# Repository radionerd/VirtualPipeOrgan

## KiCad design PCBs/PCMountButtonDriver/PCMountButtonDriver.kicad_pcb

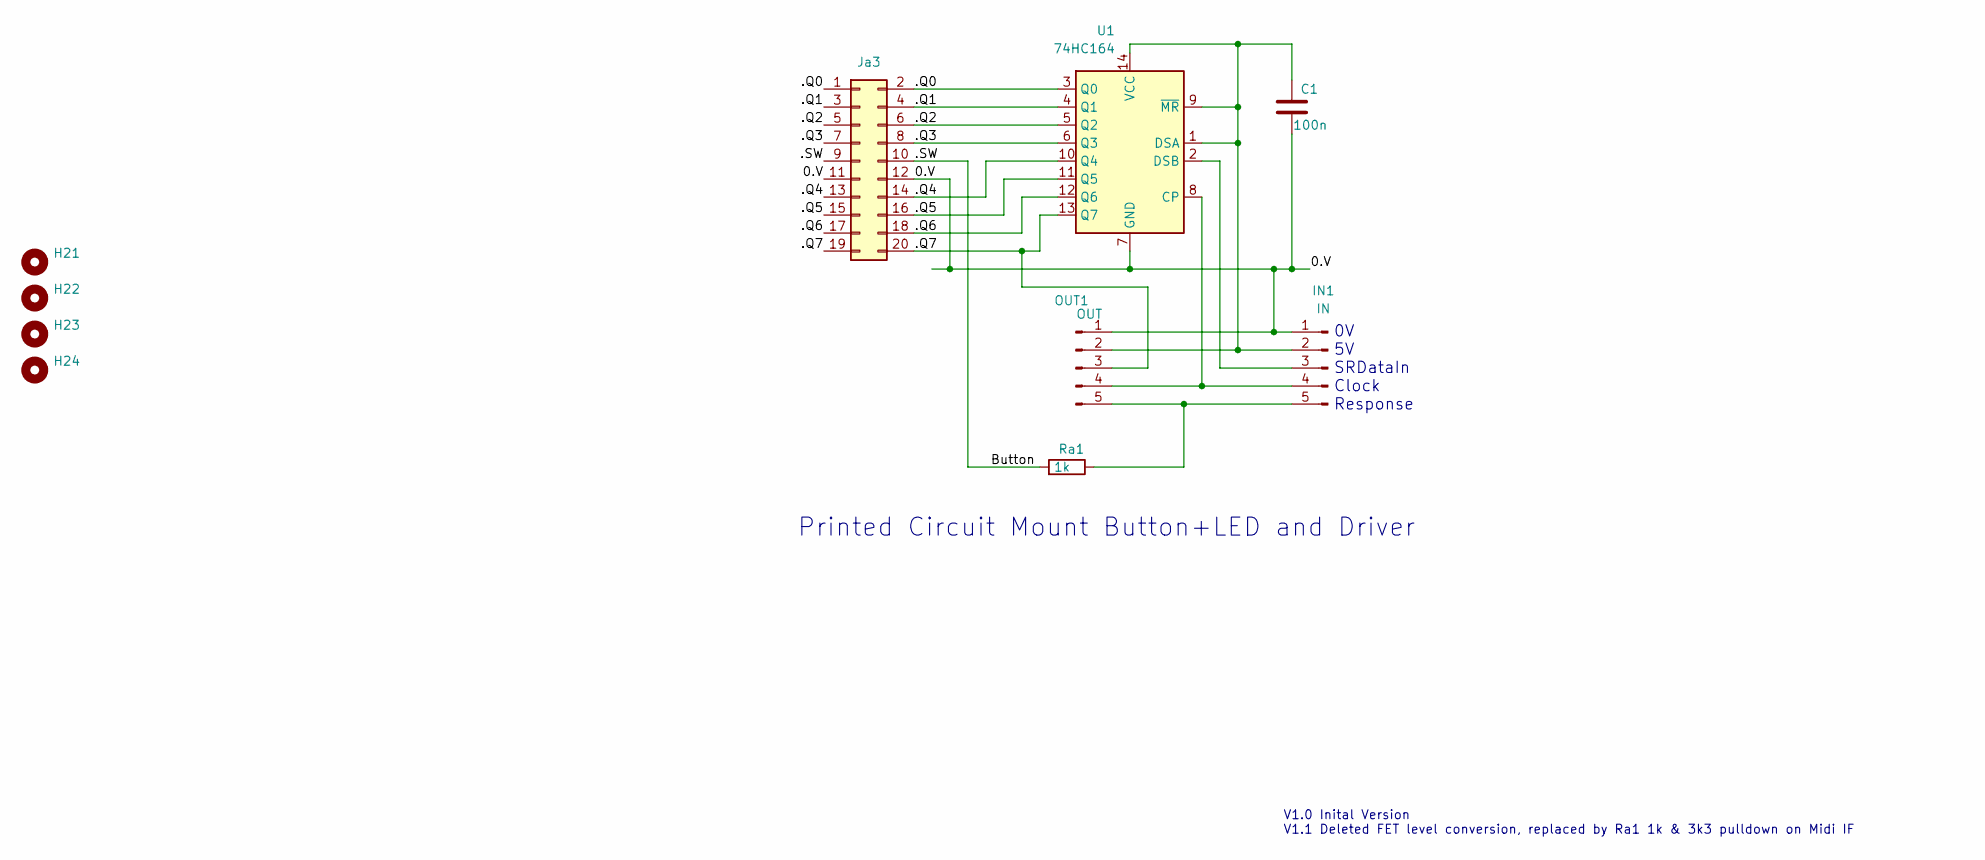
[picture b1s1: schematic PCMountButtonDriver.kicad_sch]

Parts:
C1: 100n; C_0805_2012Metric_Pad1.18x1.45mm_HandSolder
H21, H22, H23, H24: MountingHole; MountingHole_3.2mm_M3
IN1: IN; PinHeader_1x05_P2.54mm_Vertical
Ja3: Conn_02x10_Odd_Even; PinHeader_2x10_P2.54mm_Vertical
OUT1: OUT; PinHeader_1x05_P2.54mm_Vertical
Ra1: 1k; R_0805_2012Metric_Pad1.20x1.40mm_HandSolder
U1: 74HC164; DIP-14_W7.62mm_LongPads

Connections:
/0.V: C1.2, IN1.1, Ja3.11, Ja3.12, OUT1.1, U1.7 (GND)
/.Q0: Ja3.1, Ja3.2, U1.3 (Q0)
/.Q1: Ja3.3, Ja3.4, U1.4 (Q1)
/.Q2: Ja3.5, Ja3.6, U1.5 (Q2)
/.Q3: Ja3.7, Ja3.8, U1.6 (Q3)
/.Q4: Ja3.13, Ja3.14, U1.10 (Q4)
/.Q5: Ja3.15, Ja3.16, U1.11 (Q5)
/.Q6: Ja3.17, Ja3.18, U1.12 (Q6)
/.Q7: Ja3.19, Ja3.20, OUT1.3, U1.13 (Q7)
/.SW: Ja3.9, Ja3.10, Ra1.2
unnamed: C1.1, IN1.2, OUT1.2, U1.1 (DSA), U1.9 (~MR), U1.14 (VCC)
unnamed: IN1.3, U1.2 (DSB)
unnamed: IN1.4, OUT1.4, U1.8 (CP)
unnamed: IN1.5, OUT1.5, Ra1.1

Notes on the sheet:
V1.0 Inital Version V1.1 Deleted FET level conversion, replaced by Ra1 1k & 3k3 pulldown on Midi IF
Printed Circuit Mount Button+LED and Driver
0V 5V SRDataIn Clock Response

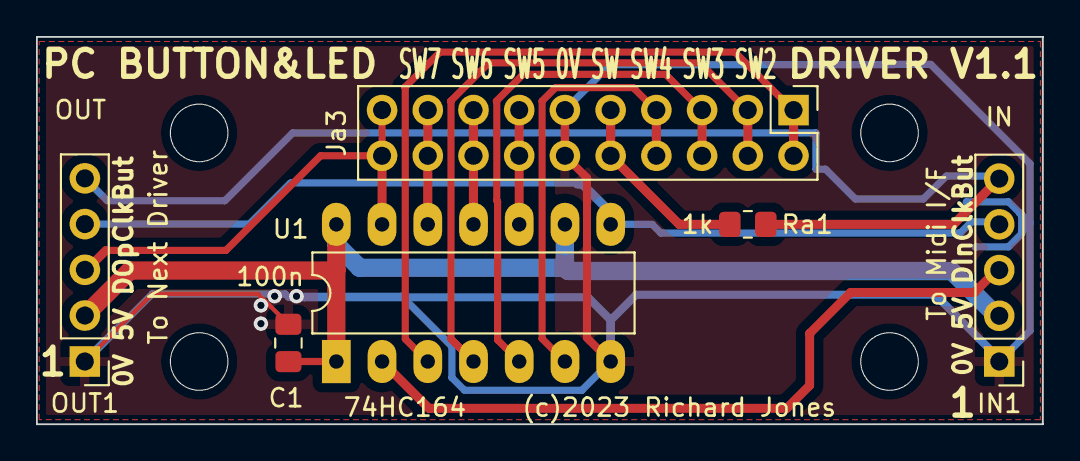
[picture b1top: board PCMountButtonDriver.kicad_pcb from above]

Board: 2 copper layers, 55.9 x 21.5 mm, 10 parts (0 on the bottom side), 14 nets.

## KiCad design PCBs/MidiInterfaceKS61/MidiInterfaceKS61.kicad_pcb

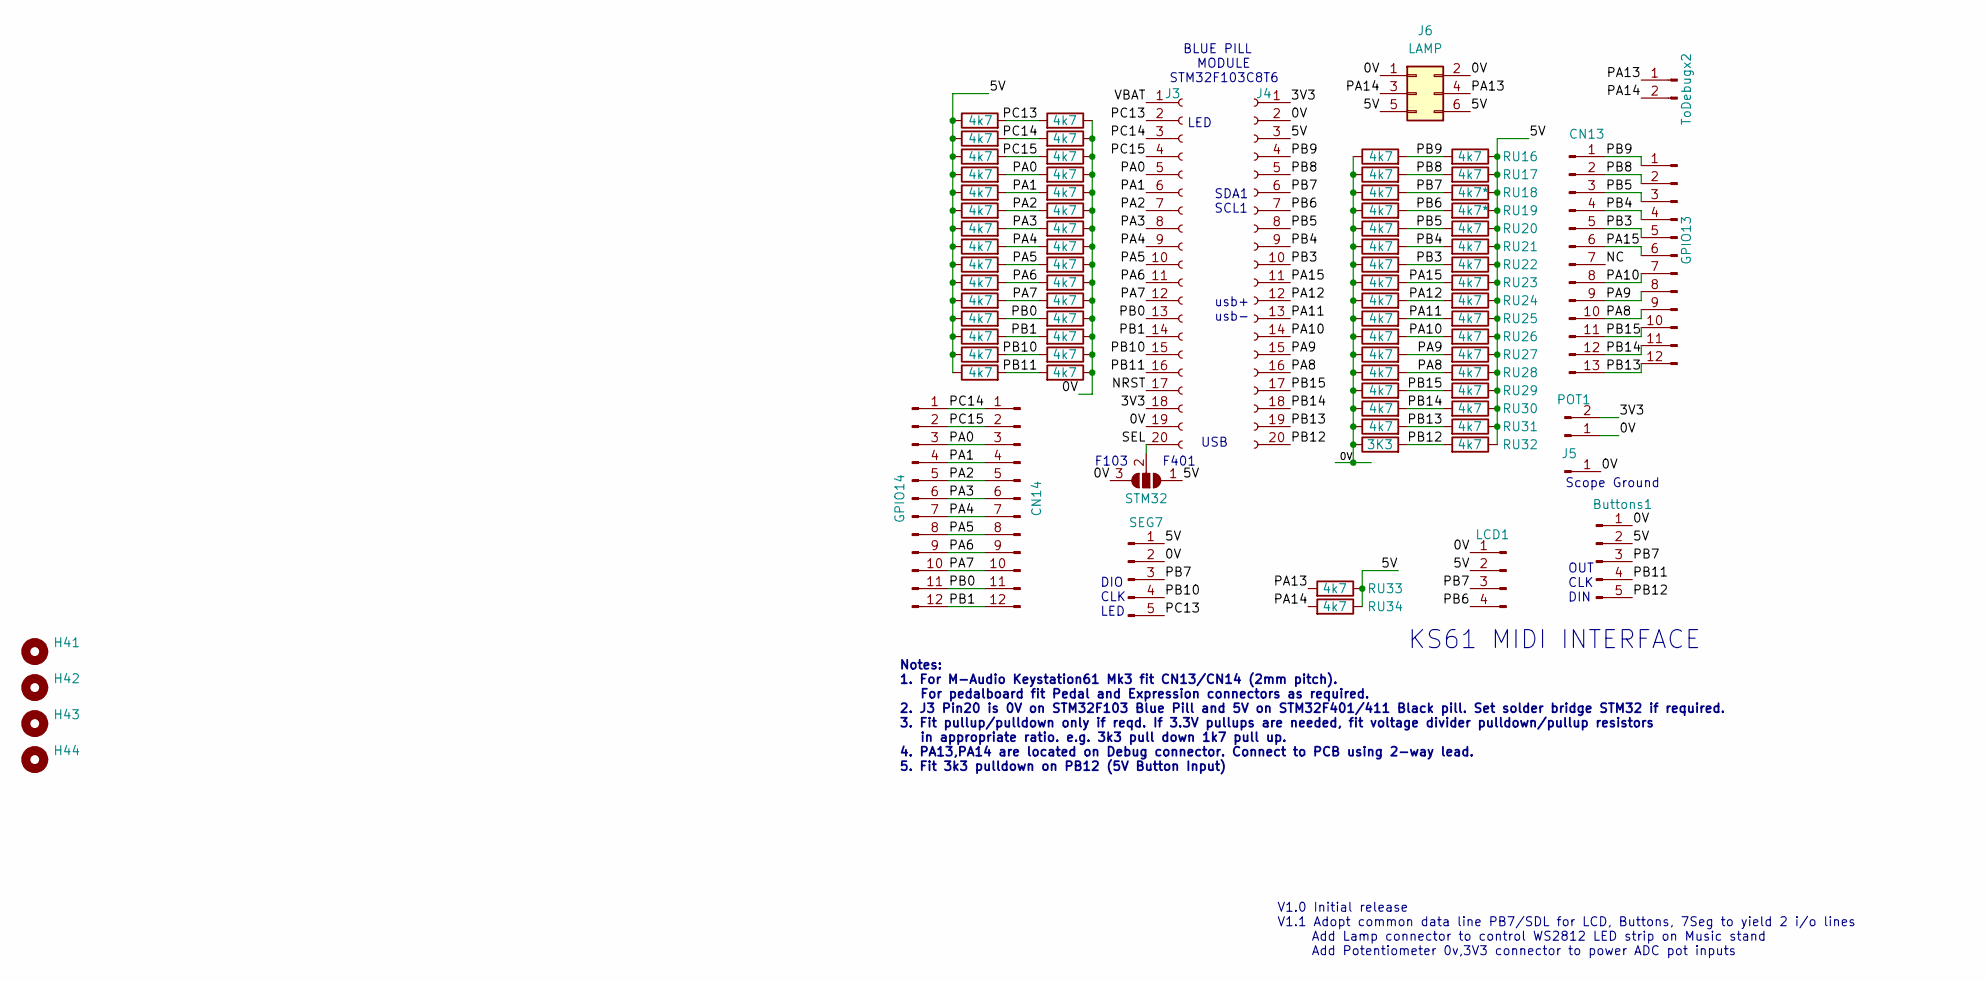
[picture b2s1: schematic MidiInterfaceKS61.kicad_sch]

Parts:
Buttons1: Conn_01x05_Male; PinHeader_1x05_P2.54mm_Vertical
CN13: Conn_01x13_Male; PinHeader_1x13_P2.00mm_Vertical
CN14: Conn_01x12_Male; PinHeader_1x12_P2.00mm_Vertical
GPIO13, GPIO14: Conn_01x12_Male; PinHeader_1x12_P2.54mm_Vertical
H41, H42, H43, H44: MountingHole; MountingHole_3.2mm_M3
J3, J4: Conn_01x20_Female; PinHeader_1x20_P2.54mm_Vertical
J5: Conn_01x01_Male; PinHeader_1x01_P2.54mm_Vertical
J6: LAMP; PinHeader_2x03_P2.54mm_Vertical
LCD1: Conn_01x04_Male; PinHeader_1x04_P2.54mm_Vertical
POT1: Conn_01x02_Male; PinHeader_1x02_P2.54mm_Vertical
RD1, RD2, RD3, RD4, RD5, RD6, RD7, RD8, RD9, RD10, RD11, RD12, RD13, RD14, RD15, RD16, RD17, RD18, RD19, RD20, RD21, RD22, RD23, RD24, RD25, RD26, RD27, RD28, RD29, RD30, RD31: 4k7; R_0805_2012Metric_Pad1.20x1.40mm_HandSolder
RD32: 3K3; R_0805_2012Metric_Pad1.20x1.40mm_HandSolder
RU1, RU2, RU3, RU4, RU5, RU6, RU7, RU8, RU9, RU10, RU11, RU12, RU13, RU14, RU15, RU16, RU17, RU20, RU21, RU22, RU23, RU24, RU25, RU26, RU27, RU28, RU29, RU30, RU31, RU32, RU33, RU34: 4k7; R_0805_2012Metric_Pad1.20x1.40mm_HandSolder
RU18, RU19: 4k7*; R_0805_2012Metric_Pad1.20x1.40mm_HandSolder
SEG7: Conn_01x05_Male; PinHeader_1x05_P2.54mm_Vertical
STM32: SolderJumper_3_Open; SolderJumper-3_P1.3mm_Open_RoundedPad1.0x1.5mm_NumberLabels
ToDebugx2: Conn_01x02_Male; PinHeader_1x02_P2.54mm_Vertical

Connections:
/0V: Buttons1.1, J3.19, J4.2, J5.1, J6.1, J6.2, LCD1.1, POT1.1, RD1.1, RD2.1, RD3.1, RD4.1, RD5.1, RD6.1, RD7.1, RD8.1, RD9.1, RD10.1, RD11.1, RD12.1, RD13.1, RD14.1, RD15.1, RD16.1, RD17.1, RD18.1, RD19.1, RD20.1, RD21.1, RD22.1, RD23.1, RD24.1, RD25.1, RD26.1, RD27.1, RD28.1, RD29.1, RD30.1, RD31.1, RD32.1, SEG7.2, STM32.3 (B)
/3V3: J3.18, J4.1, POT1.2
/5V: Buttons1.2, J4.3, J6.5, J6.6, LCD1.2, RU1.1, RU2.1, RU3.1, RU4.1, RU5.1, RU6.1, RU7.1, RU8.1, RU9.1, RU10.1, RU11.1, RU12.1, RU13.1, RU14.1, RU15.1, RU16.1, RU17.1, RU18.1, RU19.1, RU20.1, RU21.1, RU22.1, RU23.1, RU24.1, RU25.1, RU26.1, RU27.1, RU28.1, RU29.1, RU30.1, RU31.1, RU32.1, RU33.1, RU34.1, SEG7.1, STM32.1 (A)
/NC: CN13.7
/NRST: J3.17
/PA0: CN14.3, GPIO14.3, J3.5, RD4.2, RU4.2
/PA1: CN14.4, GPIO14.4, J3.6, RD5.2, RU5.2
/PA2: CN14.5, GPIO14.5, J3.7, RD6.2, RU6.2
/PA3: CN14.6, GPIO14.6, J3.8, RD7.2, RU7.2
/PA4: CN14.7, GPIO14.7, J3.9, RD8.2, RU8.2
/PA5: CN14.8, GPIO14.8, J3.10, RD9.2, RU9.2
/PA6: CN14.9, GPIO14.9, J3.11, RD10.2, RU10.2
/PA7: CN14.10, GPIO14.10, J3.12, RD11.2, RU11.2
/PA8: CN13.10, GPIO13.9, J4.16, RD28.2, RU28.2
/PA9: CN13.9, GPIO13.8, J4.15, RD27.2, RU27.2
/PA10: CN13.8, GPIO13.7, J4.14, RD26.2, RU26.2
/PA11: J4.13, RD25.2, RU25.2
/PA12: J4.12, RD24.2, RU24.2
/PA13: J6.4, RU33.2, ToDebugx2.1
/PA14: J6.3, RU34.2, ToDebugx2.2
/PA15: CN13.6, GPIO13.6, J4.11, RD23.2, RU23.2
/PB0: CN14.11, GPIO14.11, J3.13, RD12.2, RU12.2
/PB1: CN14.12, GPIO14.12, J3.14, RD13.2, RU13.2
/PB3: CN13.5, GPIO13.5, J4.10, RD22.2, RU22.2
/PB4: CN13.4, GPIO13.4, J4.9, RD21.2, RU21.2
/PB5: CN13.3, GPIO13.3, J4.8, RD20.2, RU20.2
/PB6: J4.7, LCD1.4, RD19.2, RU19.2
/PB7: Buttons1.3, J4.6, LCD1.3, RD18.2, RU18.2, SEG7.3
/PB8: CN13.2, GPIO13.2, J4.5, RD17.2, RU17.2
/PB9: CN13.1, GPIO13.1, J4.4, RD16.2, RU16.2
/PB10: J3.15, RD14.2, RU14.2, SEG7.4
/PB11: Buttons1.4, J3.16, RD15.2, RU15.2
/PB12: Buttons1.5, J4.20, RD32.2, RU32.2
/PB13: CN13.13, GPIO13.12, J4.19, RD31.2, RU31.2
/PB14: CN13.12, GPIO13.11, J4.18, RD30.2, RU30.2
/PB15: CN13.11, GPIO13.10, J4.17, RD29.2, RU29.2
/PC13: J3.2, RD1.2, RU1.2, SEG7.5
/PC14: CN14.1, GPIO14.1, J3.3, RD2.2, RU2.2
/PC15: CN14.2, GPIO14.2, J3.4, RD3.2, RU3.2
/SEL: J3.20, STM32.2 (C)
/VBAT: J3.1

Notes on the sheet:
BLUE PILL MODULE STM32F103C8T6
OUT CLK DIN
KS61 MIDI INTERFACE
usb+ usb-
DIO CLK LED
LED
Notes: 1. For M-Audio Keystation61 Mk3 fit CN13/CN14 (2mm pitch). For pedalboard fit Pedal and Expression connectors as required. 2. J3 Pin20 is 0V on STM32F103 Blue Pill and 5V on STM32F401/411 Black pill. Set solder bridge STM32 if required. 3. Fit pullup/pulldown only if reqd. If 3.3V pullups ar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
Scope Ground
SDA1 SCL1
V1.0 Initial release V1.1 Adopt common data line PB7/SDL for LCD, Buttons, 7Seg to yield 2 i/o lines Add Lamp connector to control WS2812 LED strip on Music stand Add Potentiometer 0v,3V3 connector to power ADC pot inputs
USB
F103 F401

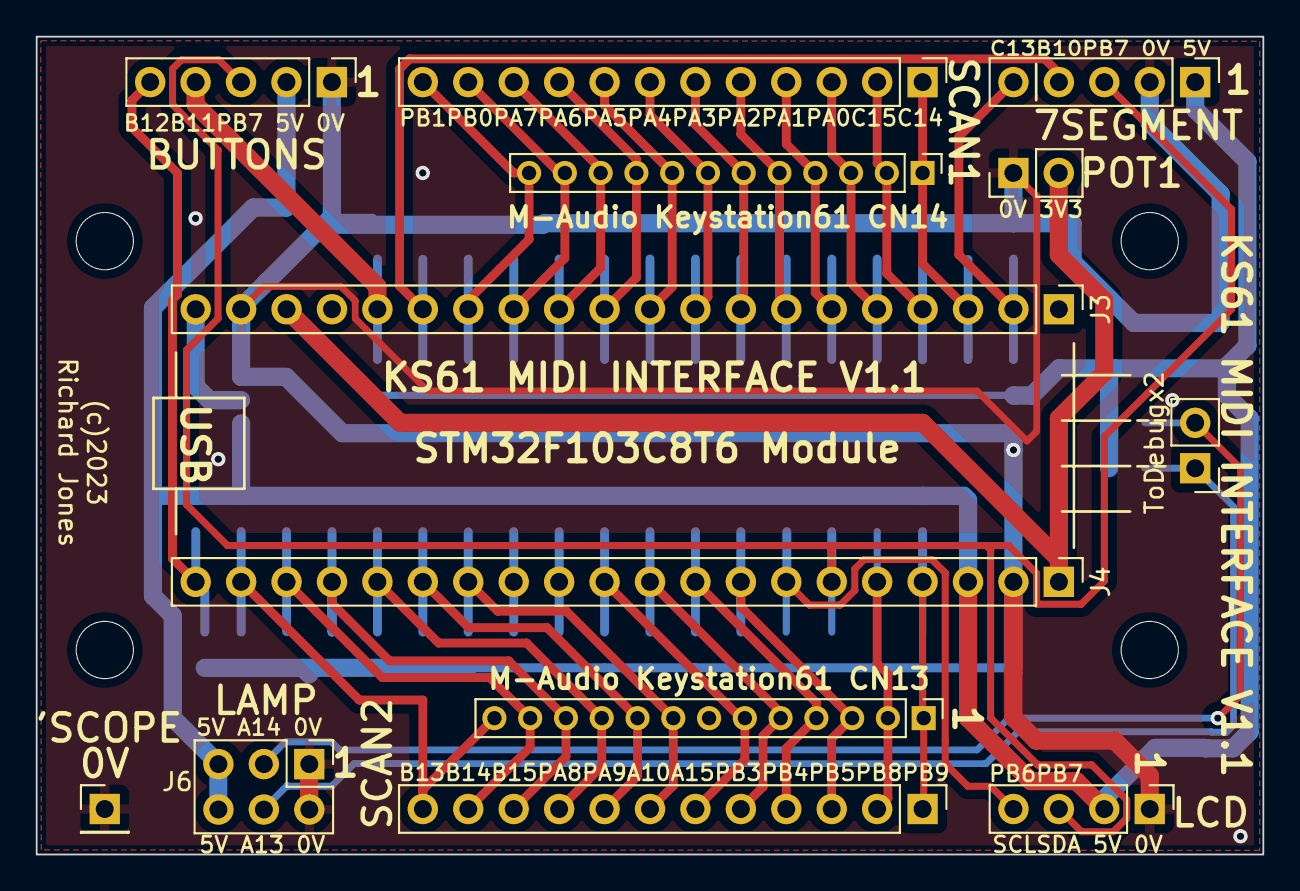
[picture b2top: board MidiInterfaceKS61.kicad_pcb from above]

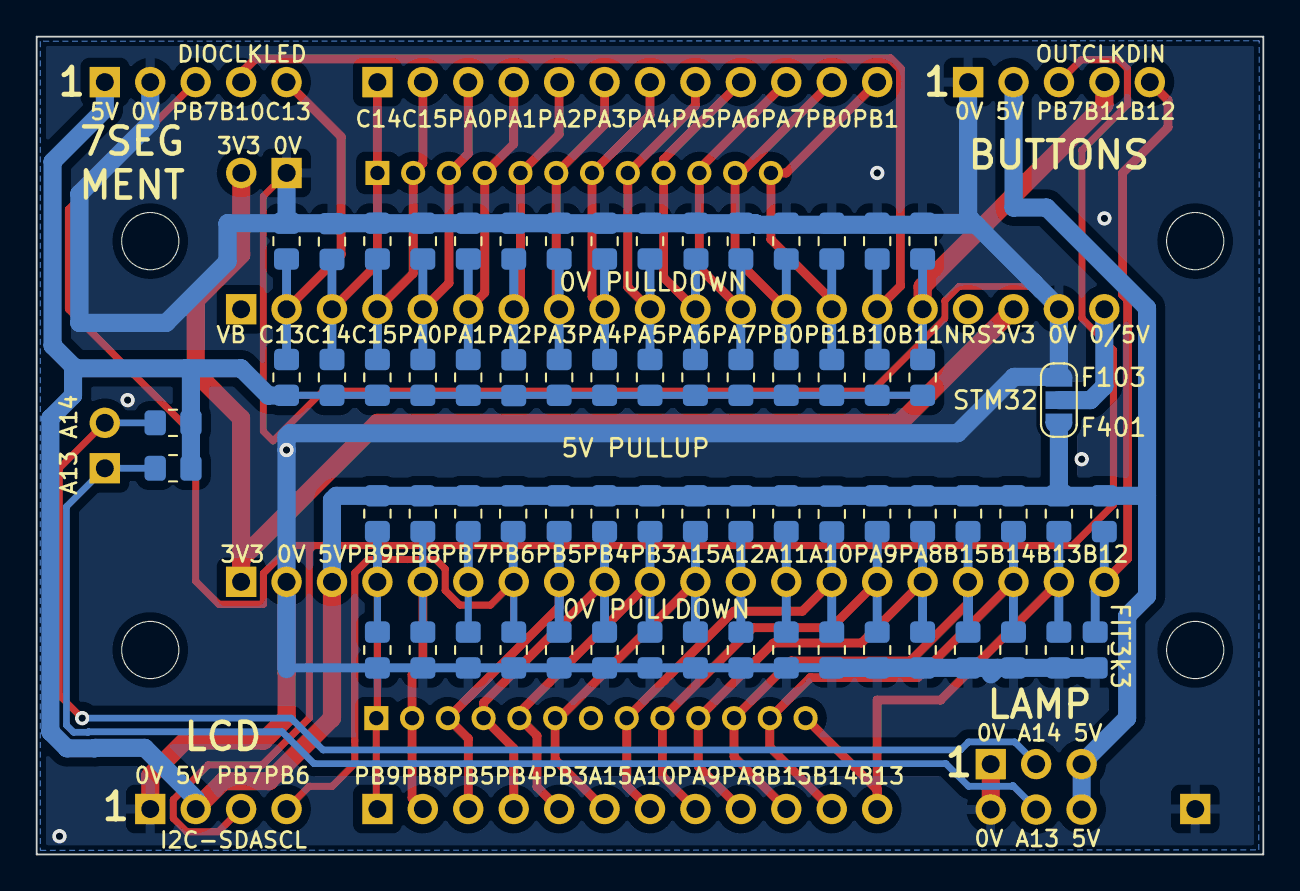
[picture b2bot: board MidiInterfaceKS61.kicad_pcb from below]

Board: 2 copper layers, 68.6 x 45.7 mm, 84 parts (67 on the bottom side), 38 nets.

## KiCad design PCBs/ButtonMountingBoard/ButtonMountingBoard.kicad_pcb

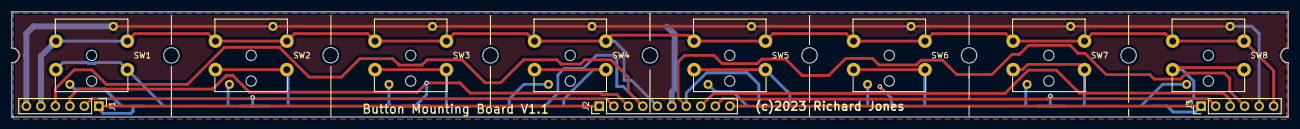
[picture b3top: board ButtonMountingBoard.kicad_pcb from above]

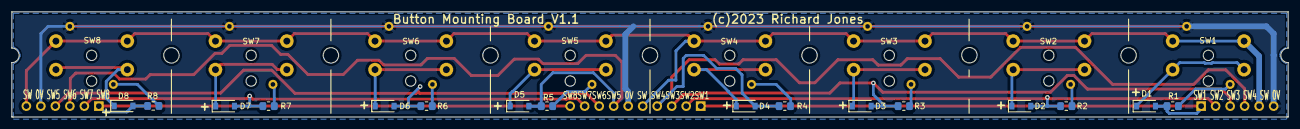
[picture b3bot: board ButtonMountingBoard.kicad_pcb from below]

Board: 2 copper layers, 223.5 x 18.4 mm, 34 parts (16 on the bottom side), 26 nets.

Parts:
D1, D2, D3, D4, D5, D6, D7, D8: 1N4148; D_SOD-123
H1, H2, H3, H4, H5, H6, H7: MountingHole; MountingHole_2.7mm_M2.5
J1, J3: Conn_01x06_Male; PinHeader_1x06_P2.54mm_Vertical
J2: Conn_01x10_Male; PinHeader_1x10_P2.54mm_Vertical
R1, R2, R3, R4, R5, R6, R7, R8: 560; R_0805_2012Metric_Pad1.20x1.40mm_HandSolder
SW1, SW2, SW3, SW4, SW5, SW6, SW7, SW8: SW_TACT_LED; TS12_TS27

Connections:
/LED: J1.6, J2.6, J3.5, SW1.5, SW2.5, SW3.5, SW4.5, SW5.5, SW6.5, SW7.5, SW8.5
/SW: J1.5, J2.5, J3.6, SW1.3, SW1.4, SW2.3, SW2.4, SW3.3, SW3.4, SW4.3, SW4.4, SW5.3, SW5.4, SW6.3, SW6.4, SW7.3, SW7.4, SW8.3, SW8.4
unnamed: D1.1 (K), SW1.1, SW1.2
unnamed: D1.2 (A), J1.1, J2.1, R1.2
unnamed: D2.1 (K), SW2.1, SW2.2
unnamed: D2.2 (A), J1.2, J2.2, R2.2
unnamed: D3.1 (K), SW3.1, SW3.2
unnamed: D3.2 (A), J1.3, J2.3, R3.2
unnamed: D4.1 (K), SW4.1, SW4.2
unnamed: D4.2 (A), J1.4, J2.4, R4.2
unnamed: D5.1 (K), SW5.1, SW5.2
unnamed: D5.2 (A), J2.7, J3.4, R5.2
unnamed: D6.1 (K), SW6.1, SW6.2
unnamed: D6.2 (A), J2.8, J3.3, R6.2
unnamed: D7.1 (K), SW7.1, SW7.2
unnamed: D7.2 (A), J2.9, J3.2, R7.2
unnamed: D8.1 (K), SW8.1, SW8.2
unnamed: D8.2 (A), J2.10, J3.1, R8.2
unnamed: R1.1, SW1.6
unnamed: R2.1, SW2.6
unnamed: R3.1, SW3.6
unnamed: R4.1, SW4.6
unnamed: R5.1, SW5.6
unnamed: R6.1, SW6.6
unnamed: R7.1, SW7.6
unnamed: R8.1, SW8.6

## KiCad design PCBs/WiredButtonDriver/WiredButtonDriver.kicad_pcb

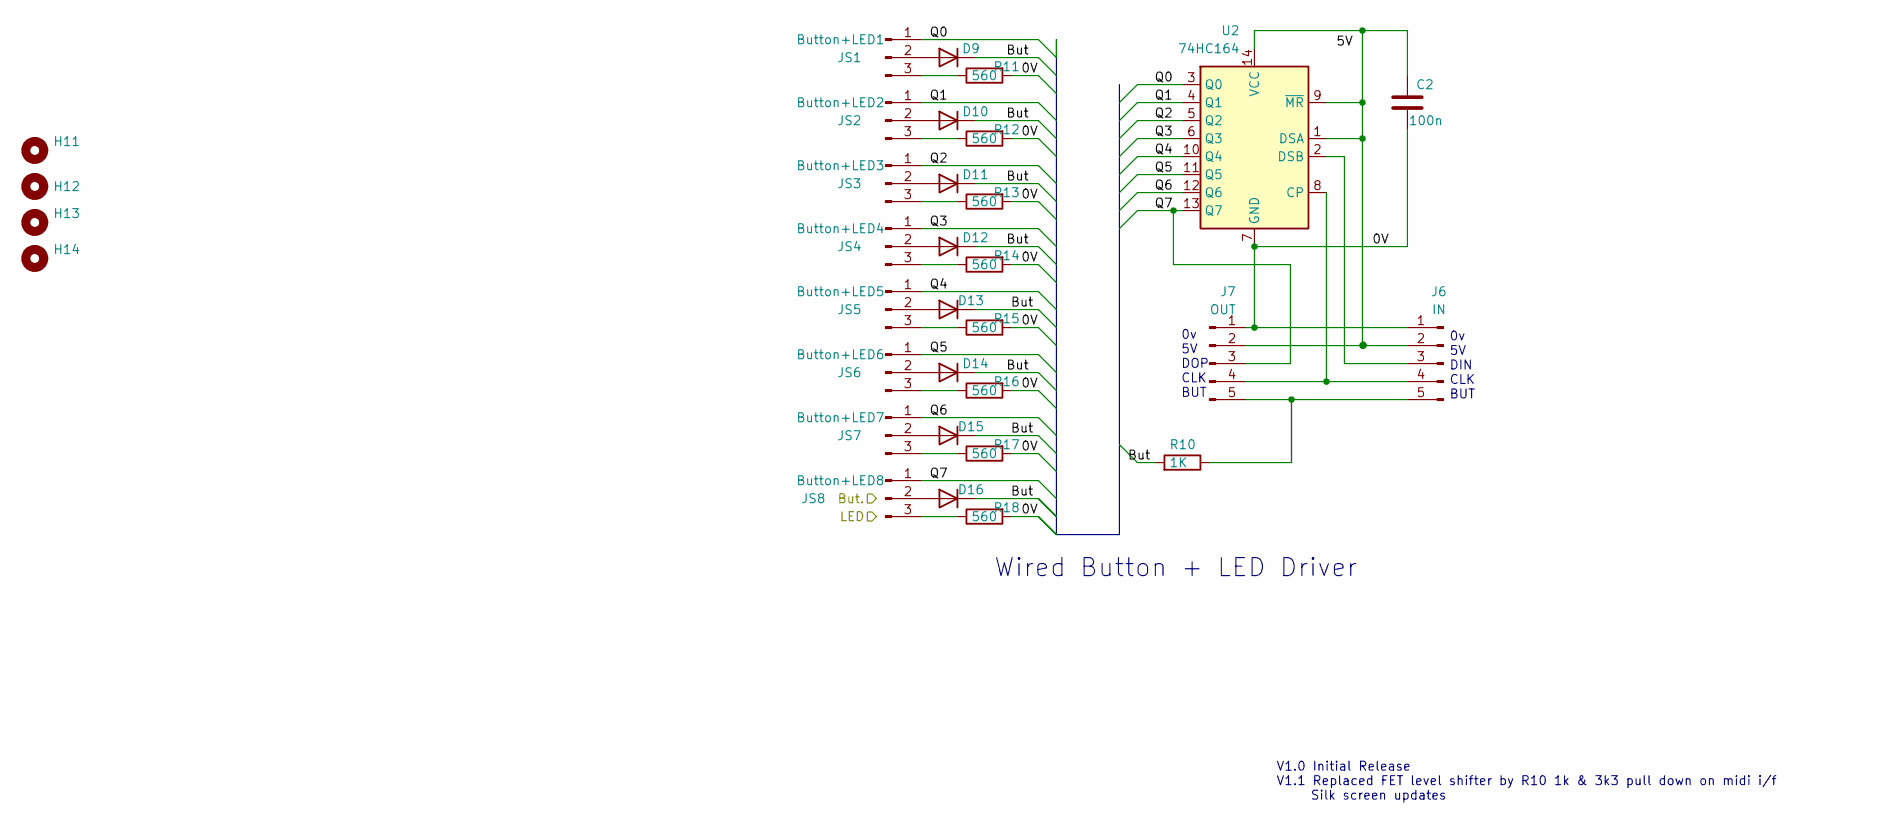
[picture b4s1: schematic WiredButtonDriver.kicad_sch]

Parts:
C2: 100n; C_0805_2012Metric_Pad1.18x1.45mm_HandSolder
D9, D10, D11, D12, D13, D14, D15, D16: 1N4148; D_SOD-123
H11, H12, H13, H14: MountingHole; MountingHole_3.2mm_M3
J6: IN; PinHeader_1x05_P2.54mm_Vertical
J7: OUT; PinHeader_1x05_P2.54mm_Vertical
JS1: Button+LED1; PinHeader_1x03_P2.54mm_Vertical
JS2: Button+LED2; PinHeader_1x03_P2.54mm_Vertical
JS3: Button+LED3; PinHeader_1x03_P2.54mm_Vertical
JS4: Button+LED4; PinHeader_1x03_P2.54mm_Vertical
JS5: Button+LED5; PinHeader_1x03_P2.54mm_Vertical
JS6: Button+LED6; PinHeader_1x03_P2.54mm_Vertical
JS7: Button+LED7; PinHeader_1x03_P2.54mm_Vertical
JS8: Button+LED8; PinHeader_1x03_P2.54mm_Vertical
R10: 1K; R_0805_2012Metric_Pad1.20x1.40mm_HandSolder
R11, R12, R13, R14, R15, R16, R17, R18: 560; R_0805_2012Metric_Pad1.20x1.40mm_HandSolder
U2: 74HC164; DIP-14_W7.62mm_LongPads

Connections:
/0V: C2.2, J6.1, J7.1, R11.2, R12.2, R13.2, R14.2, R15.2, R16.2, R17.2, R18.2, U2.7 (GND)
/But: D9.1 (K), D10.1 (K), D11.1 (K), D12.1 (K), D13.1 (K), D14.1 (K), D15.1 (K), D16.1 (K), R10.2
/Q0: JS1.1, U2.3 (Q0)
/Q1: JS2.1, U2.4 (Q1)
/Q2: JS3.1, U2.5 (Q2)
/Q3: JS4.1, U2.6 (Q3)
/Q4: JS5.1, U2.10 (Q4)
/Q5: JS6.1, U2.11 (Q5)
/Q6: JS7.1, U2.12 (Q6)
/Q7: J7.3, JS8.1, U2.13 (Q7)
unnamed: C2.1, J6.2, J7.2, U2.1 (DSA), U2.9 (~MR), U2.14 (VCC)
unnamed: D9.2 (A), JS1.2
unnamed: D10.2 (A), JS2.2
unnamed: D11.2 (A), JS3.2
unnamed: D12.2 (A), JS4.2
unnamed: D13.2 (A), JS5.2
unnamed: D14.2 (A), JS6.2
unnamed: D15.2 (A), JS7.2
unnamed: D16.2 (A), JS8.2
unnamed: J6.3, U2.2 (DSB)
unnamed: J6.4, J7.4, U2.8 (CP)
unnamed: J6.5, J7.5, R10.1
unnamed: JS1.3, R11.1
unnamed: JS2.3, R12.1
unnamed: JS3.3, R13.1
unnamed: JS4.3, R14.1
unnamed: JS5.3, R15.1
unnamed: JS6.3, R16.1
unnamed: JS7.3, R17.1
unnamed: JS8.3, R18.1

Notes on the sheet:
0v 5V DOP CLK BUT
0v 5V DIN CLK BUT
V1.0 Initial Release V1.1 Replaced FET level shifter by R10 1k & 3k3 pull down on midi i/f Silk screen updates
Wired Button + LED Driver

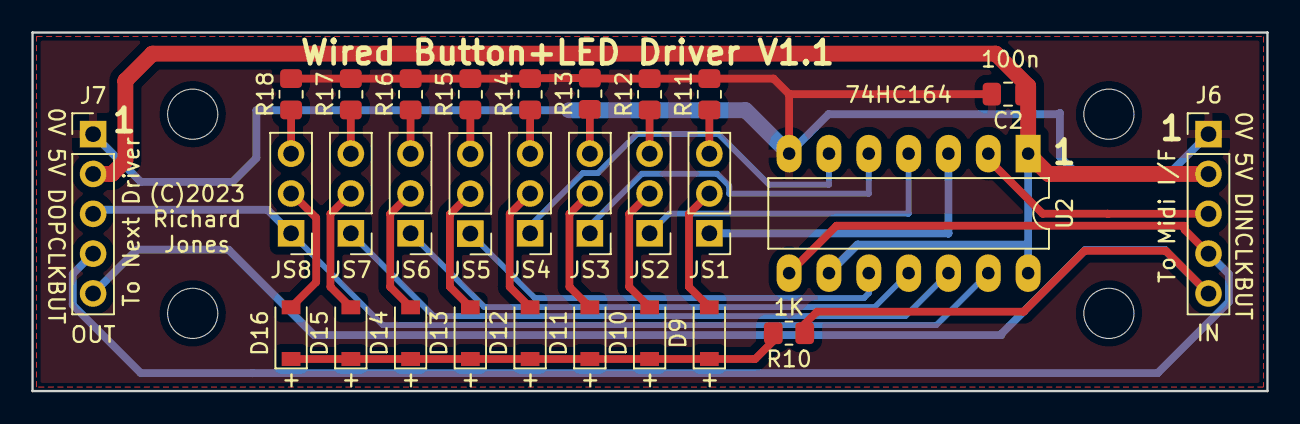
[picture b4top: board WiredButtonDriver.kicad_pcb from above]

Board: 2 copper layers, 78.7 x 22.9 mm, 33 parts (0 on the bottom side), 30 nets.

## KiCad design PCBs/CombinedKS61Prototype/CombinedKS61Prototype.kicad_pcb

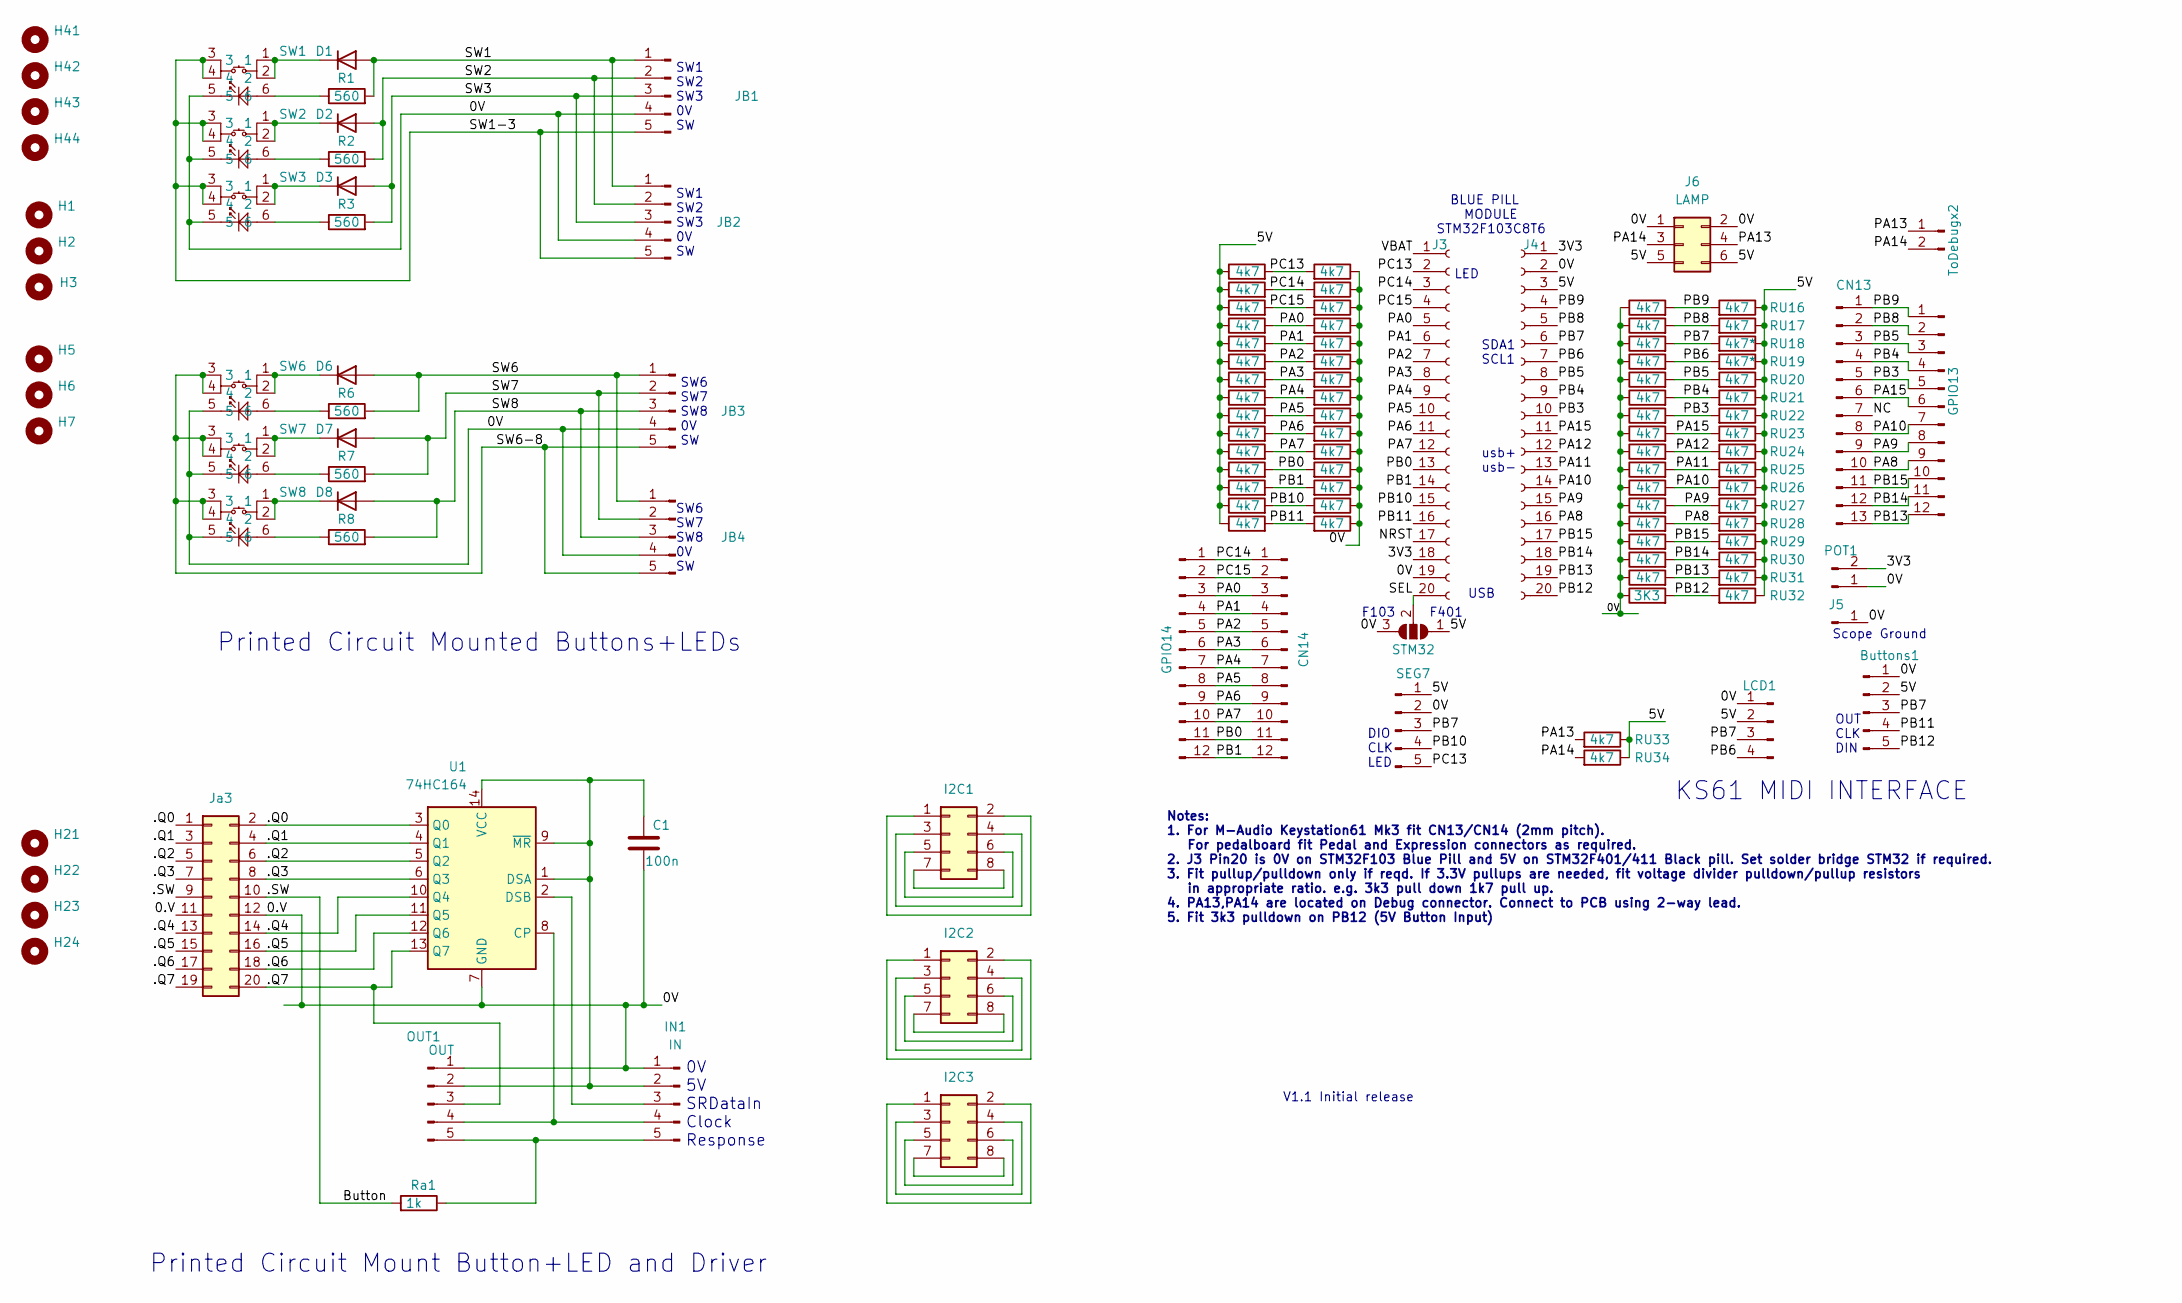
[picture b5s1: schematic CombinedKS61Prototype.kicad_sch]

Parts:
Buttons1: Conn_01x05_Male; PinHeader_1x05_P2.54mm_Vertical
C1: 100n; C_0805_2012Metric_Pad1.18x1.45mm_HandSolder
CN13: Conn_01x13_Male; PinHeader_1x13_P2.00mm_Vertical
CN14: Conn_01x12_Male; PinHeader_1x12_P2.00mm_Vertical
D1, D2, D3, D6, D7, D8: 1N4148; D_SOD-123
GPIO13, GPIO14: Conn_01x12_Male; PinHeader_1x12_P2.54mm_Vertical
H1, H2, H3, H5, H6, H7: MountingHole; MountingHole_2.7mm_M2.5
H21, H22, H23, H24, H41, H42, H43, H44: MountingHole; MountingHole_3.2mm_M3
I2C1, I2C2, I2C3: Conn_02x04_Odd_Even; PinHeader_2x04_P2.54mm_Vertical
IN1: IN; PinHeader_1x05_P2.54mm_Vertical
J3, J4: Conn_01x20_Female; PinHeader_1x20_P2.54mm_Vertical
J5: Conn_01x01_Male; PinHeader_1x01_P2.54mm_Vertical
J6: LAMP; PinHeader_2x03_P2.54mm_Vertical
JB1, JB2, JB3, JB4: Conn_01x05_Male; PinHeader_1x05_P2.54mm_Vertical
Ja3: Conn_02x10_Odd_Even; PinHeader_2x10_P2.54mm_Vertical
LCD1: Conn_01x04_Male; PinHeader_1x04_P2.54mm_Vertical
OUT1: OUT; PinHeader_1x05_P2.54mm_Vertical
POT1: Conn_01x02_Male; PinHeader_1x02_P2.54mm_Vertical
R1, R2, R3, R6, R7, R8: 560; R_0805_2012Metric_Pad1.20x1.40mm_HandSolder
RD1, RD2, RD3, RD4, RD5, RD6, RD7, RD8, RD9, RD10, RD11, RD12, RD13, RD14, RD15, RD16, RD17, RD18, RD19, RD20, RD21, RD22, RD23, RD24, RD25, RD26, RD27, RD28, RD29, RD30, RD31: 4k7; R_0805_2012Metric_Pad1.20x1.40mm_HandSolder
RD32: 3K3; R_0805_2012Metric_Pad1.20x1.40mm_HandSolder
RU1, RU2, RU3, RU4, RU5, RU6, RU7, RU8, RU9, RU10, RU11, RU12, RU13, RU14, RU15, RU16, RU17, RU20, RU21, RU22, RU23, RU24, RU25, RU26, RU27, RU28, RU29, RU30, RU31, RU32, RU33, RU34: 4k7; R_0805_2012Metric_Pad1.20x1.40mm_HandSolder
RU18, RU19: 4k7*; R_0805_2012Metric_Pad1.20x1.40mm_HandSolder
Ra1: 1k; R_0805_2012Metric_Pad1.20x1.40mm_HandSolder
SEG7: Conn_01x05_Male; PinHeader_1x05_P2.54mm_Vertical
STM32: SolderJumper_3_Open; SolderJumper-3_P1.3mm_Open_RoundedPad1.0x1.5mm_NumberLabels
SW1, SW2, SW3, SW6, SW7, SW8: SW_TACT_LED; TS12_TS27
ToDebugx2: Conn_01x02_Male; PinHeader_1x02_P2.54mm_Vertical
U1: 74HC164; DIP-14_W7.62mm_LongPads

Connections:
/0.V: Buttons1.1, C1.2, IN1.1, J3.19, J4.2, J5.1, J6.1, J6.2, JB1.4, JB2.4, JB3.4, JB4.4, Ja3.11, Ja3.12, LCD1.1, OUT1.1, POT1.1, RD1.1, RD2.1, RD3.1, RD4.1, RD5.1, RD6.1, RD7.1, RD8.1, RD9.1, RD10.1, RD11.1, RD12.1, RD13.1, RD14.1, RD15.1, RD16.1, RD17.1, RD18.1, RD19.1, RD20.1, RD21.1, RD22.1, RD23.1, RD24.1, RD25.1, RD26.1, RD27.1, RD28.1, RD29.1, RD30.1, RD31.1, RD32.1, SEG7.2, STM32.3 (B), SW1.5, SW2.5, SW3.5, SW6.5, SW7.5, SW8.5, U1.7 (GND)
/3V3: J3.18, J4.1, POT1.2
/5V: Buttons1.2, J4.3, J6.5, J6.6, LCD1.2, RU1.1, RU2.1, RU3.1, RU4.1, RU5.1, RU6.1, RU7.1, RU8.1, RU9.1, RU10.1, RU11.1, RU12.1, RU13.1, RU14.1, RU15.1, RU16.1, RU17.1, RU18.1, RU19.1, RU20.1, RU21.1, RU22.1, RU23.1, RU24.1, RU25.1, RU26.1, RU27.1, RU28.1, RU29.1, RU30.1, RU31.1, RU32.1, RU33.1, RU34.1, SEG7.1, STM32.1 (A)
/.Q0: Ja3.1, Ja3.2, U1.3 (Q0)
/.Q1: Ja3.3, Ja3.4, U1.4 (Q1)
/.Q2: Ja3.5, Ja3.6, U1.5 (Q2)
/.Q3: Ja3.7, Ja3.8, U1.6 (Q3)
/.Q4: Ja3.13, Ja3.14, U1.10 (Q4)
/.Q5: Ja3.15, Ja3.16, U1.11 (Q5)
/.Q6: Ja3.17, Ja3.18, U1.12 (Q6)
/.Q7: Ja3.19, Ja3.20, OUT1.3, U1.13 (Q7)
/.SW: Ja3.9, Ja3.10, Ra1.2
/NC: CN13.7
/NRST: J3.17
/PA0: CN14.3, GPIO14.3, J3.5, RD4.2, RU4.2
/PA1: CN14.4, GPIO14.4, J3.6, RD5.2, RU5.2
/PA2: CN14.5, GPIO14.5, J3.7, RD6.2, RU6.2
/PA3: CN14.6, GPIO14.6, J3.8, RD7.2, RU7.2
/PA4: CN14.7, GPIO14.7, J3.9, RD8.2, RU8.2
/PA5: CN14.8, GPIO14.8, J3.10, RD9.2, RU9.2
/PA6: CN14.9, GPIO14.9, J3.11, RD10.2, RU10.2
/PA7: CN14.10, GPIO14.10, J3.12, RD11.2, RU11.2
/PA8: CN13.10, GPIO13.9, J4.16, RD28.2, RU28.2
/PA9: CN13.9, GPIO13.8, J4.15, RD27.2, RU27.2
/PA10: CN13.8, GPIO13.7, J4.14, RD26.2, RU26.2
/PA11: J4.13, RD25.2, RU25.2
/PA12: J4.12, RD24.2, RU24.2
/PA13: J6.4, RU33.2, ToDebugx2.1
/PA14: J6.3, RU34.2, ToDebugx2.2
/PA15: CN13.6, GPIO13.6, J4.11, RD23.2, RU23.2
/PB0: CN14.11, GPIO14.11, J3.13, RD12.2, RU12.2
/PB1: CN14.12, GPIO14.12, J3.14, RD13.2, RU13.2
/PB3: CN13.5, GPIO13.5, J4.10, RD22.2, RU22.2
/PB4: CN13.4, GPIO13.4, J4.9, RD21.2, RU21.2
/PB5: CN13.3, GPIO13.3, J4.8, RD20.2, RU20.2
/PB6: J4.7, LCD1.4, RD19.2, RU19.2
/PB7: Buttons1.3, J4.6, LCD1.3, RD18.2, RU18.2, SEG7.3
/PB8: CN13.2, GPIO13.2, J4.5, RD17.2, RU17.2
/PB9: CN13.1, GPIO13.1, J4.4, RD16.2, RU16.2
/PB10: J3.15, RD14.2, RU14.2, SEG7.4
/PB11: Buttons1.4, J3.16, RD15.2, RU15.2
/PB12: Buttons1.5, J4.20, RD32.2, RU32.2
/PB13: CN13.13, GPIO13.12, J4.19, RD31.2, RU31.2
/PB14: CN13.12, GPIO13.11, J4.18, RD30.2, RU30.2
/PB15: CN13.11, GPIO13.10, J4.17, RD29.2, RU29.2
/PC13: J3.2, RD1.2, RU1.2, SEG7.5
/PC14: CN14.1, GPIO14.1, J3.3, RD2.2, RU2.2
/PC15: CN14.2, GPIO14.2, J3.4, RD3.2, RU3.2
/SEL: J3.20, STM32.2 (C)
/SW1: D1.2 (A), JB1.1, JB2.1, R1.2
/SW1-3: JB1.5, JB2.5, SW1.3, SW1.4, SW2.3, SW2.4, SW3.3, SW3.4
/SW2: D2.2 (A), JB1.2, JB2.2, R2.2
/SW3: D3.2 (A), JB1.3, JB2.3, R3.2
/SW6: D6.2 (A), JB3.1, JB4.1, R6.2
/SW6-8: JB3.5, JB4.5, SW6.3, SW6.4, SW7.3, SW7.4, SW8.3, SW8.4
/SW7: D7.2 (A), JB3.2, JB4.2, R7.2
/SW8: D8.2 (A), JB3.3, JB4.3, R8.2
/VBAT: J3.1
unnamed: C1.1, IN1.2, OUT1.2, U1.1 (DSA), U1.9 (~MR), U1.14 (VCC)
unnamed: D1.1 (K), SW1.1, SW1.2
unnamed: D2.1 (K), SW2.1, SW2.2
unnamed: D3.1 (K), SW3.1, SW3.2
unnamed: D6.1 (K), SW6.1, SW6.2
unnamed: D7.1 (K), SW7.1, SW7.2
unnamed: D8.1 (K), SW8.1, SW8.2
unnamed: I2C1.1, I2C1.2
unnamed: I2C1.3, I2C1.4
unnamed: I2C1.5, I2C1.6
unnamed: I2C1.7, I2C1.8
unnamed: I2C2.1, I2C2.2
unnamed: I2C2.3, I2C2.4
unnamed: I2C2.5, I2C2.6
unnamed: I2C2.7, I2C2.8
unnamed: I2C3.1, I2C3.2
unnamed: I2C3.3, I2C3.4
unnamed: I2C3.5, I2C3.6
unnamed: I2C3.7, I2C3.8
unnamed: IN1.3, U1.2 (DSB)
unnamed: IN1.4, OUT1.4, U1.8 (CP)
unnamed: IN1.5, OUT1.5, Ra1.1
unnamed: R1.1, SW1.6
unnamed: R2.1, SW2.6
unnamed: R3.1, SW3.6
unnamed: R6.1, SW6.6
unnamed: R7.1, SW7.6
unnamed: R8.1, SW8.6

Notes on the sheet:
Printed Circuit Mount Button+LED and Driver
BLUE PILL MODULE STM32F103C8T6
Scope Ground
usb+ usb-
V1.1 Initial release
OUT CLK DIN
Printed Circuit Mounted Buttons+LEDs
SW1 SW2 SW3 0V SW
SDA1 SCL1
USB
Notes: 1. For M-Audio Keystation61 Mk3 fit CN13/CN14 (2mm pitch). For pedalboard fit Pedal and Expression connectors as required. 2. J3 Pin20 is 0V on STM32F103 Blue Pill and 5V on STM32F401/411 Black pill. Set solder bridge STM32 if required. 3. Fit pullup/pulldown only if reqd. If 3.3V pullups ar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
0V 5V SRDataIn Clock Response
DIO CLK LED
KS61 MIDI INTERFACE
LED
SW6 SW7 SW8 0V SW
F103 F401

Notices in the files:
PCBs/ButtonMountingBoard/ButtonMountingBoard.kicad_pcb:
(c)2023 Richard Jones
PCBs/CombinedKS61Prototype/CombinedKS61Prototype.kicad_pcb:
(c)2023
